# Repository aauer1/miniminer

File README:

MiniMiner One                            Copyright 2013 by Andreas Auer

It is a single Avalon ASIC Bitcoin miner powered by the USB port. I 
designed it as an initial project in the Bitcoin community.

Subdirectories:

- pcb:
  This is the schematic and layout file for the PCB. You have to use
  Cadsoft Eagle to open it.

- firmware:
  The firmware for the microcontroller is based on the LUFA USB stack
  for Atmel microcontrollers.
  To compile it, enter the LUFA-120730/Projects/AvalonBTC directory
  and type "make". You need the avr-gcc to compile it.

- bfgminer-driver:
  This directory includes the driver files for bfgminer. You have to 
  copy it to the bfgminer directory and modify the configure.ac file
  to get it compiled. 
  The driver is old and not compatible with an actual version of 
  bfgminer. It was developed with bfgminer 3.1.x. To run it on a newer
  version you have to modify it massively!

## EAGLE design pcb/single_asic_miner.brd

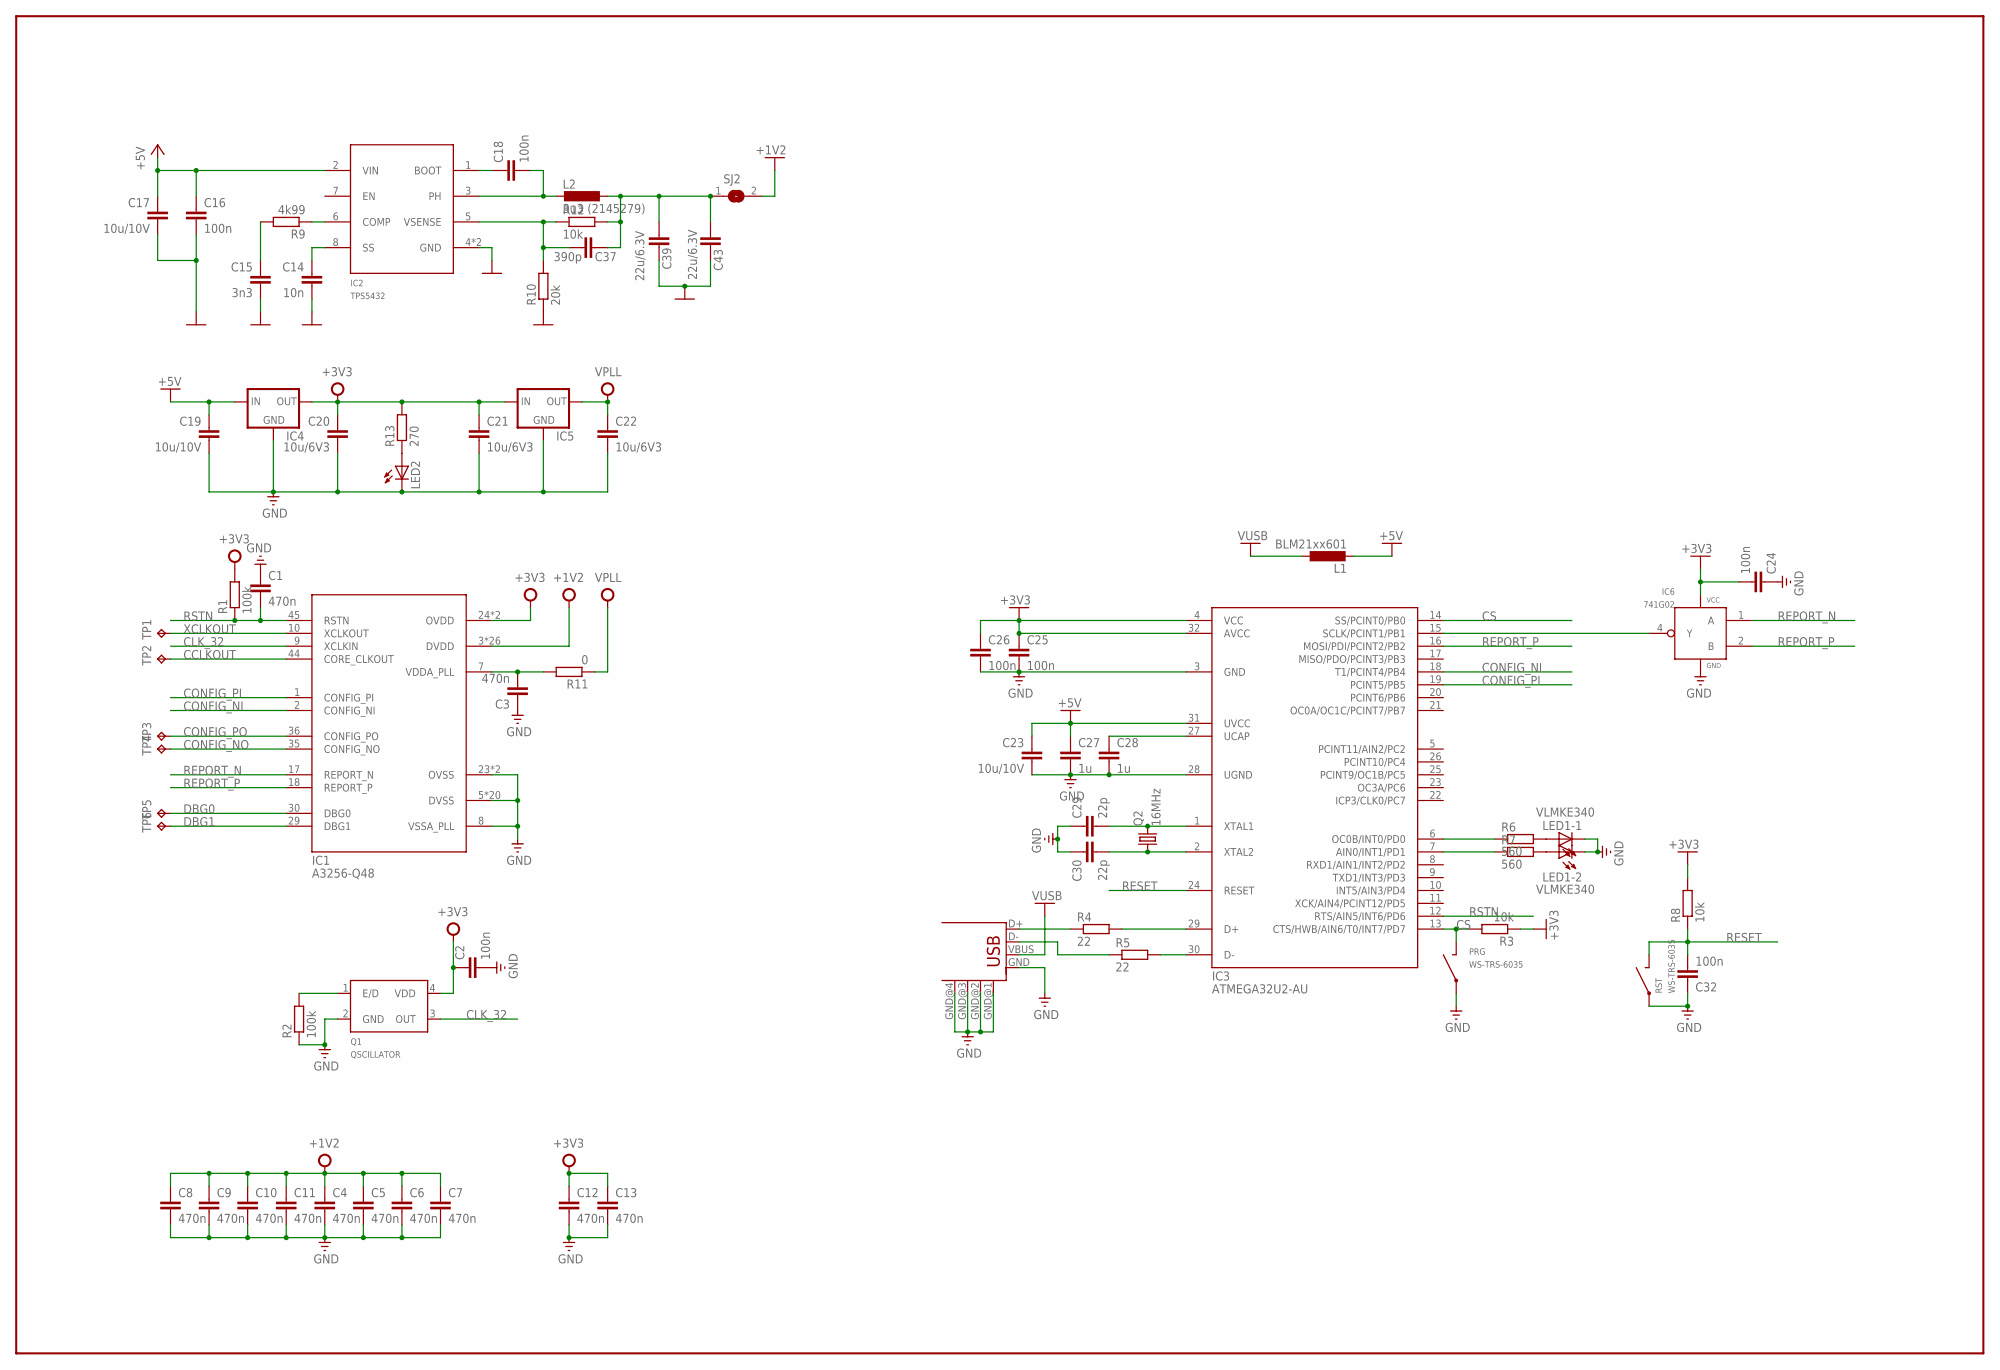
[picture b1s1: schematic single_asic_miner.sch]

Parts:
C1, C3, C4, C5, C6, C7, C8, C9, C10, C11, C12, C13: 470n; C0805
C2, C16, C18, C24, C25, C26, C32: 100n; C0805
C14: 10n; C0805
C15: 3n3; C0805
C17, C19, C23: 10u/10V; C0805
C20, C21, C22: 10u/6V3; C0805
C27, C28: 1u; C0805
C29, C30: 22p; C0805
C37: 390p; C0805
C39, C43: 22u/6.3V; C0805
IC1: A3256-Q48; QFN48
IC2: TPS5432; SO08E
IC3: ATMEGA32U2-AU; TQFP32
IC4, IC5: LM1117; SOT223
IC6: 741G02; SOT23-5
L1: BLM21xx601; L0805
L2: 3u3 (2145279); L4540
LED1: VLMKE340; PLCC4
LED2: LEDCHIP-LED0805; CHIP-LED0805
PRG: WS-TRS-6035; WS-TRS
Q1: QSCILLATOR; SMD7552
Q2: 16MHz; 6035
R1, R2: 100k; R0805
R3, R8, R12: 10k; R0805
R4, R5: 22; R0805
R6, R7: 560; R0805
R9: 4k99; R0805
R10: 20k; R0805
R11: 0; R0805
R13: 270; R0805
RST: WS-TRS-6035; WS-TRS
SJ2: SJ
TP1, TP2, TP3, TP4, TP5, TP6: TPB1,27; B1,27
X1: USB-SHIELD-1; USB-M-S1_1

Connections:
+1V2: C4.1, C5.1, C6.1, C7.1, C8.1, C9.1, C10.1, C11.1, IC1.3 (DVDD), IC1.4 (DVDD), IC1.6 (DVDD), IC1.11 (DVDD), IC1.12 (DVDD), IC1.13 (DVDD), IC1.14 (DVDD), IC1.15 (DVDD), IC1.16 (DVDD), IC1.19 (DVDD), IC1.21 (DVDD), IC1.22 (DVDD), IC1.25 (DVDD), IC1.26 (DVDD), IC1.27 (DVDD), IC1.28 (DVDD), IC1.31 (DVDD), IC1.33 (DVDD), IC1.34 (DVDD), IC1.39 (DVDD), IC1.40 (DVDD), IC1.41 (DVDD), IC1.43 (DVDD), IC1.46 (DVDD), IC1.47 (DVDD), IC1.48 (DVDD), SJ2.2
+3V3: C2.1, C12.1, C13.1, C20.1, C21.1, C24.2, C25.1, C26.1, IC1.24 (OVDD), IC1.37 (OVDD), IC3.4 (VCC), IC3.32 (AVCC), IC4.2 (OUT), IC5.3 (IN), IC6.5 (VCC), Q1.4 (VDD), R1.2, R3.1, R8.2, R13.2
+5V: C16.1, C17.1, C19.1, C23.1, C27.1, IC2.2 (VIN), IC3.31 (UVCC), IC4.3 (IN), L1.2
CCLKOUT: IC1.44 (CORE_CLKOUT), TP2.TP
CLK_32: IC1.9 (XCLKIN), Q1.3 (OUT)
CONFIG_NI: IC1.2 (CONFIG_NI), IC3.18 (T1/PCINT4/PB4)
CONFIG_NO: IC1.35 (CONFIG_NO), TP4.TP
CONFIG_PI: IC1.1 (CONFIG_PI), IC3.19 (PCINT5/PB5)
CONFIG_PO: IC1.36 (CONFIG_PO), TP3.TP
CS: IC3.13 (CTS/HWB/AIN6/T0/INT7/PD7), IC3.14 (SS/PCINT0/PB0), PRG.P$2, R3.2
D+: IC3.29 (D+), R4.2
D-: IC3.30 (D-), R5.2
DBG0: IC1.30 (DBG0), TP5.TP
DBG1: IC1.29 (DBG1), TP6.TP
GND: C1.1, C2.2, C3.1, C4.2, C5.2, C6.2, C7.2, C8.2, C9.2, C10.2, C11.2, C12.2, C13.2, C14.2, C15.2, C16.2, C17.2, C19.2, C20.2, C21.2, C22.2, C23.2, C24.1, C25.2, C26.2, C27.2, C28.2, C29.1, C30.1, C32.1, C39.2, C43.2, IC1.5 (DVSS), IC1.8 (VSSA_PLL), IC1.20 (DVSS), IC1.23 (OVSS), IC1.32 (DVSS), IC1.38 (OVSS), IC1.42 (DVSS), IC1.P$1 (DVSS), IC1.P$2 (DVSS), IC1.P$3 (DVSS), IC1.P$4 (DVSS), IC1.P$5 (DVSS), IC1.P$6 (DVSS), IC1.P$7 (DVSS), IC1.P$8 (DVSS), IC1.P$9 (DVSS), IC1.P$10 (DVSS), IC1.P$11 (DVSS), IC1.P$12 (DVSS), IC1.P$13 (DVSS), IC1.P$14 (DVSS), IC1.P$15 (DVSS), IC1.P$16 (DVSS), IC2.4 (GND), IC2.E (GND), IC3.3 (GND), IC3.28 (UGND), IC4.1 (GND), IC5.1 (GND), IC6.3 (GND), LED1.C1 (C), LED1.C2 (C), LED2.C, PRG.P$1, Q1.2 (GND), R2.1, R10.1, RST.P$1, X1.GND, X1.GND@1 (GND), X1.GND@2 (GND), X1.GND@3 (GND), X1.GND@4 (GND)
unnamed: IC3.15 (SCLK/PCINT1/PB1), IC6.4 (Y)
unnamed: Q1.1 (E/D), R2.2
unnamed: IC3.6 (OC0B/INT0/PD0), R6.1
unnamed: IC3.7 (AIN0/INT1/PD1), R7.1
unnamed: LED1.A1 (A), R6.2
unnamed: LED1.A2 (A), R7.2
unnamed: C3.2, IC1.7 (VDDA_PLL), R11.2
unnamed: R4.1, X1.D+
unnamed: R5.1, X1.D-
unnamed: C28.1, IC3.27 (UCAP)
unnamed: LED2.A, R13.1
unnamed: C29.2, IC3.1 (XTAL1), Q2.P$2 (2)
unnamed: C30.2, IC3.2 (XTAL2), Q2.P$1 (1)
unnamed: C14.1, IC2.8 (SS)
unnamed: IC2.6 (COMP), R9.1
unnamed: C15.1, R9.2
unnamed: C18.1, IC2.1 (BOOT)
unnamed: C18.2, IC2.3 (PH), L2.P$2 (2)
unnamed: C37.1, C39.1, C43.1, L2.P$1 (1), R12.2, SJ2.1
unnamed: C37.2, IC2.5 (VSENSE), R10.2, R12.1
REPORT_N: IC1.17 (REPORT_N), IC6.1 (A)
REPORT_P: IC1.18 (REPORT_P), IC3.16 (MOSI/PDI/PCINT2/PB2), IC6.2 (B)
RESET: C32.2, IC3.24 (RESET), R8.1, RST.P$2
RSTN: C1.2, IC1.45 (RSTN), IC3.12 (RTS/AIN5/INT6/PD6), R1.1
VPLL: C22.1, IC5.2 (OUT), R11.1
VUSB: L1.1, X1.VBUS
XCLKOUT: IC1.10 (XCLKOUT), TP1.TP

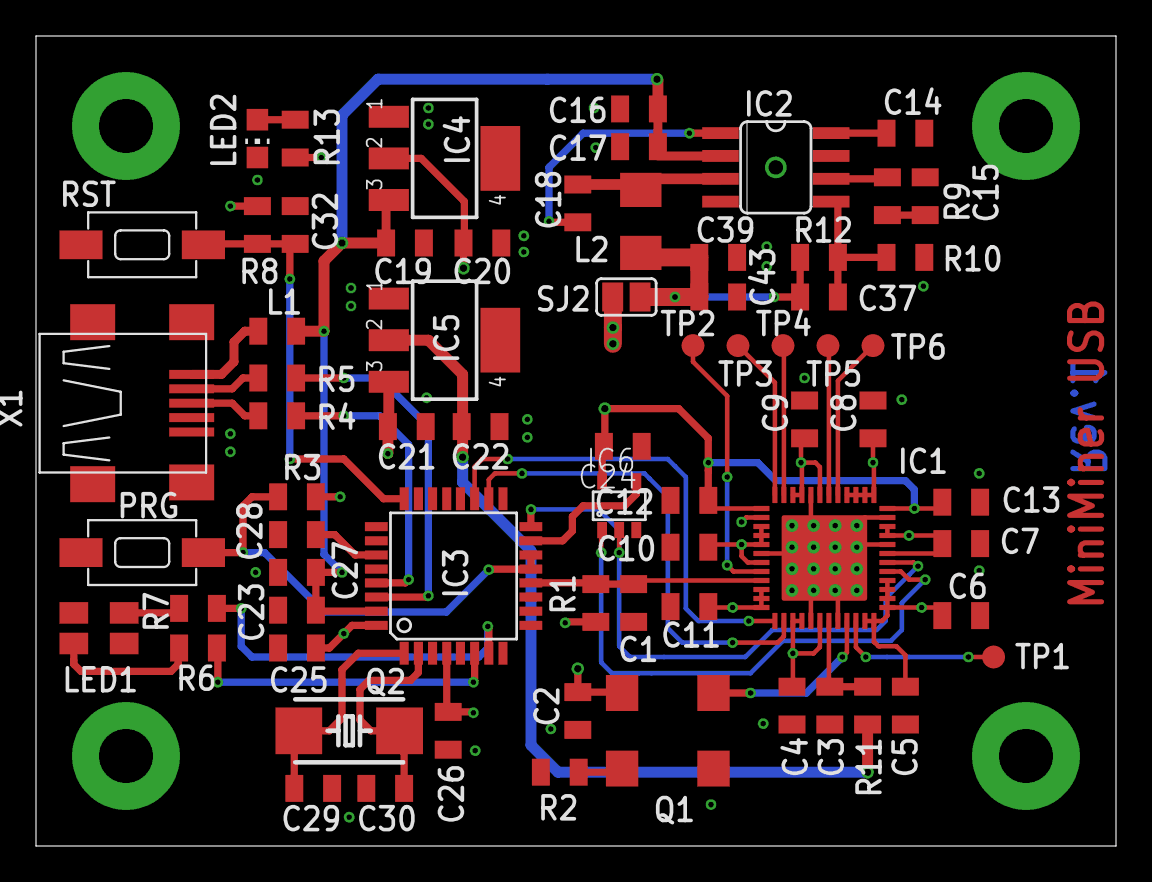
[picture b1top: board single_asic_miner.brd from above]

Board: 4 copper layers, 60.0 x 45.0 mm, 69 parts (0 on the bottom side), 42 nets.

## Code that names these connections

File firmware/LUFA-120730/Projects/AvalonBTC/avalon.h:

/*
 * avalon.h
 *
 *  Created on: 06.07.2013
 *      Author: DI Andreas Auer
 */

#ifndef AVALON_H_
#define AVALON_H_

#include <stdint.h>

#define DATA_PORT       PORTB
#define DATA_N          _BV(PB4)
#define DATA_P          _BV(PB5)

#define RESET_PORT      PORTD
#define RESET_PIN       _BV(PD6)

#define asicEnableSpi()         DDRD |=  _BV(PD7)
#define asicDisableSpi()        DDRD &= ~_BV(PD7)
#define asicIdle()              DATA_PORT |= (DATA_N | DATA_P);

void asicInit(void);
void asicReset(void);
void asicResetSpi(void);
void asicStop(void);
uint8_t asicReportValid(void);
uint32_t asicGetNonce(void);
void asicSend(uint32_t *buffer, uint8_t size);
void asicPrecalc(uint32_t *midstate, uint32_t *data, uint32_t *precalc);

#endif /* AVALON_H_ */

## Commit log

2013-11-25 MiniMiner One development files
2013-11-25 Readme file added
